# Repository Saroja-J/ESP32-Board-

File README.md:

# 📡 ESP32-WROOM-32D Development Board

A custom **ESP32-WROOM-32D Development Board** designed in **KiCad** for IoT and embedded applications. The board integrates USB-to-UART programming, power management, automatic reset and boot circuitry, and GPIO expansion, providing a compact platform for developing Wi-Fi and Bluetooth-enabled systems.

---

## 📖 Overview

This project is based on the **ESP32-WROOM-32D**, a Wi-Fi and Bluetooth-enabled microcontroller module from Espressif. The board includes a **CH340C USB-to-UART interface**, **LM2596 buck converter**, automatic reset and boot circuitry, GPIO headers, and supporting passive components. It supports **UART, SPI, I²C, PWM, ADC, and GPIO** interfaces, making it suitable for IoT, embedded systems, automation, and rapid prototyping.

---

## 📷 PCB Layout Images

> Add your PCB images below.

| 2-Layer PCB | 4-Layer PCB |
|--------------|--------------|
|  | |

---

## ⚙️ Working

1. The board is powered through USB or an external power source.
2. The **LM2596 buck converter** provides a regulated power supply for the board.
3. The **CH340C** enables USB-to-UART communication for programming and serial debugging.
4. The automatic **Reset** and **Boot** circuit allows easy firmware uploading.
5. After programming, the ESP32 communicates with external peripherals through its GPIO and communication interfaces.

---

## ✨ Features

-  ESP32-WROOM-32D Wi-Fi & Bluetooth Module
-  CH340C USB-to-UART Interface
-  LM2596 Buck Converter
-  Automatic Reset & Boot Circuit
-  GPIO Expansion Headers
-  Supports UART, SPI, I²C, PWM & ADC
-  Designed using KiCad

---

## 🛠️ Components

| Component | Description |
|-----------|-------------|
| ESP32-WROOM-32D | Main Wi-Fi & Bluetooth microcontroller |
| CH340C | USB-to-UART programming interface |
| LM2596 | Buck converter for power regulation |
| USB Connector | Power input and programming |
| NPN Transistors | Automatic Reset & Boot switching |
| Push Buttons | Manual Reset & Boot |
| Capacitors | Power filtering and decoupling |
| Resistors | Pull-up, pull-down and current limiting |
| GPIO Headers | External peripheral connections |

---

## 🚀 Applications

- 🌐 Internet of Things (IoT)
- 🏠 Home Automation
- 🤖 Robotics
- 📡 Wireless Sensor Nodes
- 📊 Data Logging
- 🎛️ Embedded System Development

---

## 📐 Design Details

- Designed by referring to the **ESP32-WROOM-32D Datasheet**, **Hardware Design Guidelines**, and supporting component datasheets.
- Recommended resistor and capacitor values were used throughout the design.
- Decoupling capacitors were placed close to the ESP32 power pins for stable operation.
- A copper-free keep-out zone was maintained around the ESP32 antenna for better RF performance.
- NPN transistors were used for the automatic **Reset** and **Boot** switching circuit.
- The **4-layer PCB** uses copper-filled planes for improved power distribution and grounding.
- Both the **2-layer** and **4-layer** PCB designs were completed with **0 DRC errors**.
- The **LM2596** buck converter was designed using its datasheet. For different input voltages or output currents, refer to the datasheet to select the appropriate inductor and capacitor values.
- An **ESD protection diode** recommended in the ESP32 Hardware Design Guidelines is **not included** in this revision and can be added in future designs.

---

## ⚠️ Warning

This design does **not** include an **ESD protection diode** on the **3.3V supply** near the **ESP32-WROOM-32D**, although it is recommended in the **ESP32 Hardware Design Guidelines**. It can be added in future revisions to improve protection against electrostatic discharge (ESD).

---

## 📄 License

This project is shared for **educational and learning purposes**.

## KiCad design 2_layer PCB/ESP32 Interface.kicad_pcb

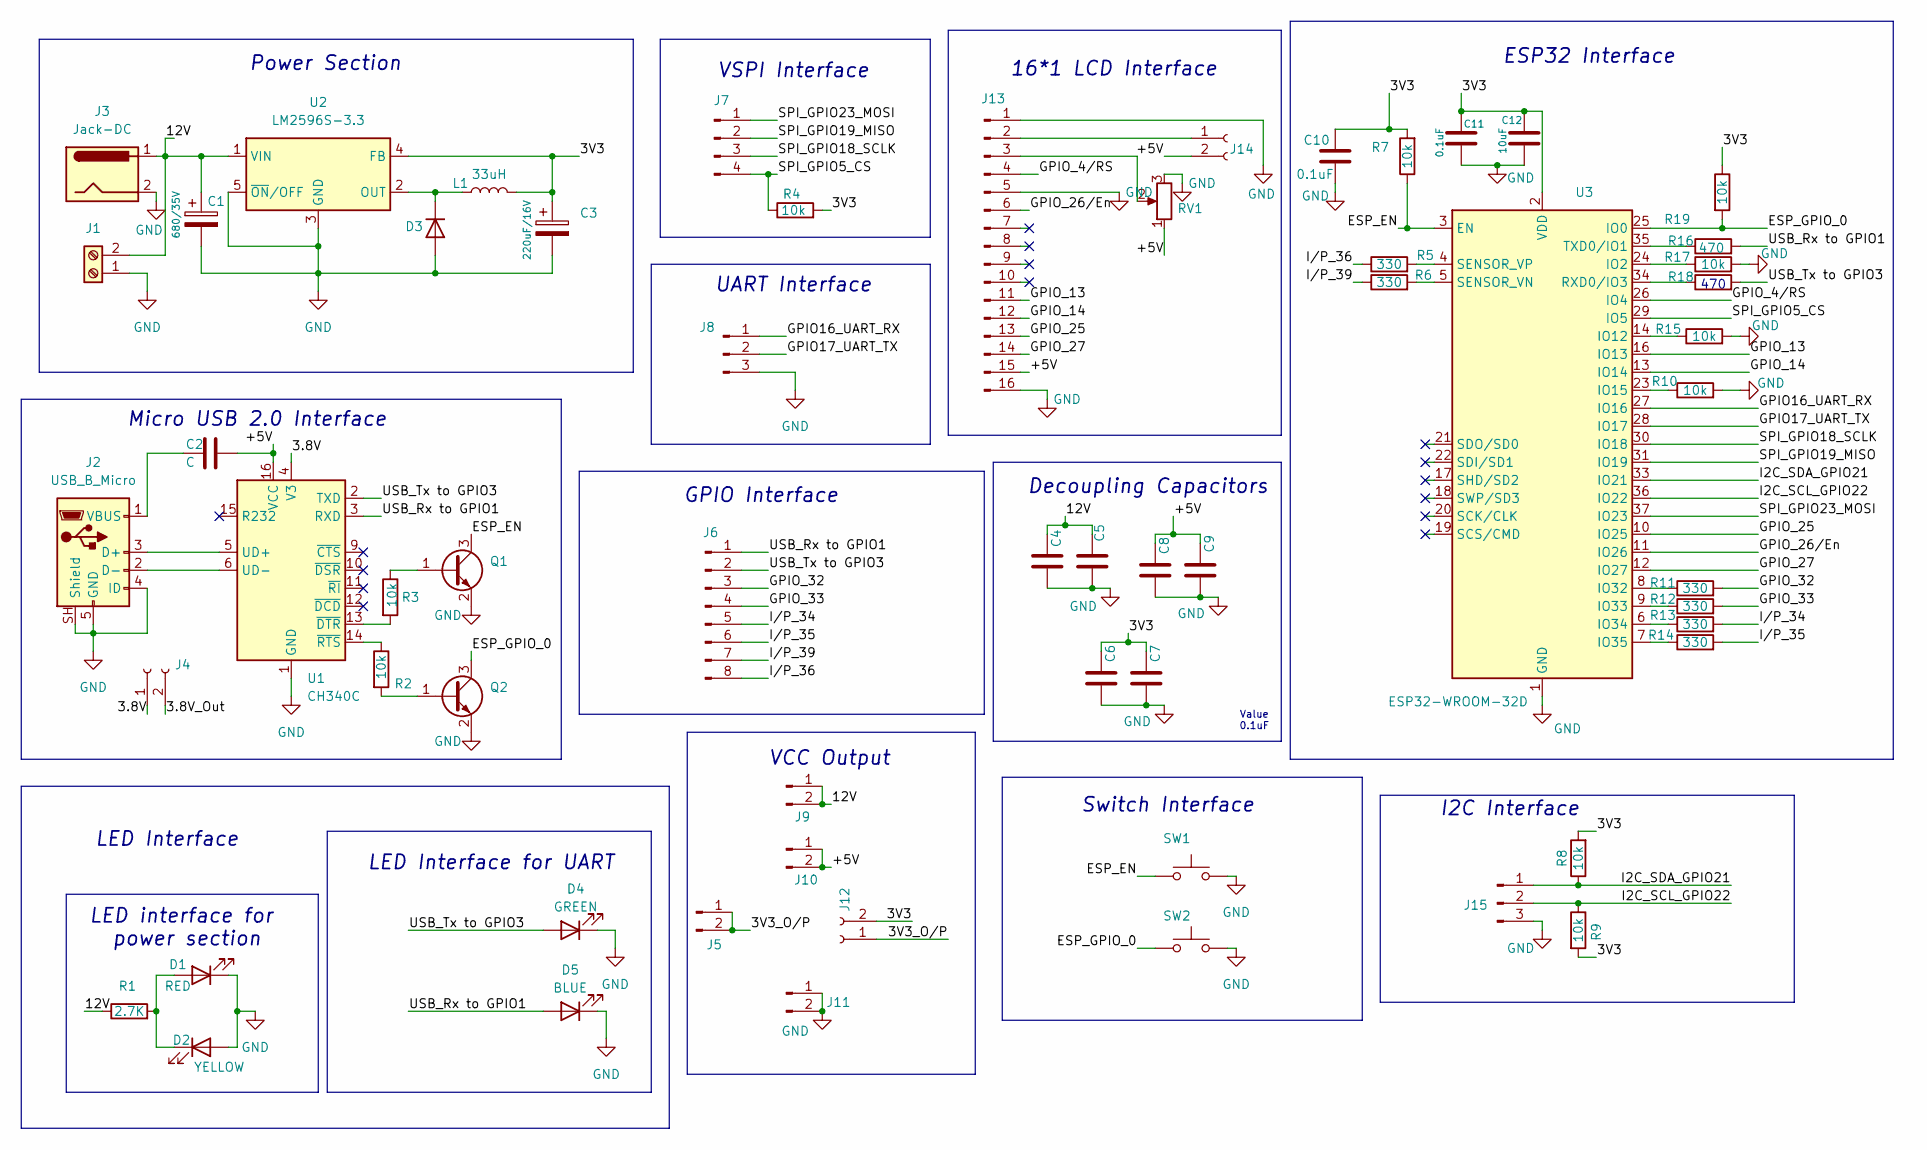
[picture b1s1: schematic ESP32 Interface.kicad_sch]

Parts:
C1: 680/35V; CP_Radial_D8.0mm_P5.00mm
C2, C5, C6, C7, C8, C9: C; C_0805_2012Metric_Pad1.18x1.45mm_HandSolder
C3: 220uF/16V; CP_Radial_D8.0mm_P2.50mm
C4, C10, C11: 0.1uF; C_0805_2012Metric_Pad1.18x1.45mm_HandSolder
C12: 10uF; C_0805_2012Metric_Pad1.18x1.45mm_HandSolder
D1: RED; LED_0805_2012Metric_Pad1.15x1.40mm_HandSolder
D2: YELLOW; LED_0805_2012Metric_Pad1.15x1.40mm_HandSolder
D3: SM518; D_T-1_P2.54mm_Vertical_AnodeUp
D4: GREEN; LED_0805_2012Metric_Pad1.15x1.40mm_HandSolder
D5: BLUE; LED_0805_2012Metric_Pad1.15x1.40mm_HandSolder
J1: Screw_Terminal_01x02; TerminalBlock_Phoenix_MKDS-1,5-2-5.08_1x02_P5.08mm_Horizont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
J2: USB_B_Micro; USB_Micro-AB_Molex_47590-0001
J3: Jack-DC; BarrelJack_SwitchcraftConxall_RAPC10U_Horizontal
J4: Conn_01x02_Socket; PinSocket_1x02_P2.54mm_Vertical
J5, J9, J10, J11: Conn_01x02_Pin; PinSocket_1x02_P2.54mm_Vertical
J6: Conn_01x08_Pin; PinSocket_1x08_P2.54mm_Vertical
J7: Conn_01x04_Pin; PinHeader_1x04_P2.54mm_Vertical
J8: Conn_01x03_Pin; PinSocket_1x03_P2.54mm_Vertical
J12: Conn_01x02_Socket; PinHeader_1x02_P2.54mm_Vertical
J13: Conn_01x16_Pin; PinHeader_1x16_P2.54mm_Vertical
J14: Conn_01x02_Socket; PinHeader_1x02_P2.00mm_Vertical
J15: Conn_01x03_Pin; PinHeader_1x03_P2.54mm_Vertical
L1: 33uH; L_0805_2012Metric_Pad1.05x1.20mm_HandSolder
Q1, Q2: MMBT2222A; SOT-23
R1: 2.7K; R_0805_2012Metric_Pad1.20x1.40mm_HandSolder
R2, R3, R4, R7, R8, R9, R10, R15, R17, R18, R19: 10k; R_0805_2012Metric_Pad1.20x1.40mm_HandSolder
R5, R6, R11, R12, R13, R14: 330; R_0805_2012Metric_Pad1.20x1.40mm_HandSolder
R16: 470; R_0805_2012Metric_Pad1.20x1.40mm_HandSolder
RV1: R_Potentiometer; Potentiometer_Vishay_148-149_Single_Horizontal
SW1, SW2: SW_Omron_B3FS; SW_TH_Tactile_Omron_B3F-100x
U1: CH340C; SOIC-16_3.9x9.9mm_P1.27mm
U2: LM2596S-3.3; TO-263-5_TabPin3
U3: ESP32-WROOM-32D

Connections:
/3.8V: J4.1, U1.4 (V3)
/3.8V_Out: J4.2
/3V3: C3.1, C6.2, C7.2, C10.1, C11.1, C12.1, J12.2, L1.2, R4.2, R7.2, R8.2, R9.2, R19.1, U2.4 (FB), U3.2 (VDD)
/3V3_O/P: J5.1, J5.2, J12.1
/12V: C1.1, C4.2, C5.2, J1.2, J3.1, J9.1, J9.2, R1.1, U2.1 (VIN)
/+5V: C2.1, C8.2, C9.2, J10.1, J10.2, J13.15, J14.2, RV1.1, U1.16 (VCC)
/ESP_EN: Q1.3 (C), R7.1, SW1.1, U3.3 (EN)
/ESP_GPIO_0: Q2.3 (C), R19.2, SW2.1, U3.25 (IO0)
/GPIO16_UART_RX: J8.1, U3.27 (IO16)
/GPIO17_UART_TX: J8.2, U3.28 (IO17)
/GPIO_4/RS: J13.4, U3.26 (IO4)
/GPIO_13: J13.11, U3.16 (IO13)
/GPIO_14: J13.12, U3.13 (IO14)
/GPIO_25: J13.13, U3.10 (IO25)
/GPIO_26/En: J13.6, U3.11 (IO26)
/GPIO_27: J13.14, U3.12 (IO27)
/GPIO_32: J6.3, R11.2
/GPIO_33: J6.4, R12.2
/I2C_SCL_GPIO22: J15.2, R9.1, U3.36 (IO22)
/I2C_SDA_GPIO21: J15.1, R8.1, U3.33 (IO21)
/I/P_34: J6.5, R13.2
/I/P_35: J6.6, R14.2
/I/P_36: J6.8, R5.1
/I/P_39: J6.7, R6.1
/SPI_GPIO5_CS: J7.4, R4.1, U3.29 (IO5)
/SPI_GPIO18_SCLK: J7.3, U3.30 (IO18)
/SPI_GPIO19_MISO: J7.2, U3.31 (IO19)
/SPI_GPIO23_MOSI: J7.1, U3.37 (IO23)
/USB_Rx to GPIO1: D5.2 (A), J6.1, R16.2, U1.3 (RXD)
/USB_Tx to GPIO3: D4.2 (A), J6.2, R18.2, U1.2 (TXD)
GND: C1.2, C3.2, C4.1, C5.1, C6.1, C7.1, C8.1, C9.1, C10.2, C11.2, C12.2, D1.1 (K), D2.2 (A), D3.2 (A), D4.1 (K), D5.1 (K), J1.1, J2.4 (ID), J2.5 (GND), J2.SH (Shield), J3.2, J8.3, J11.1, J11.2, J13.1, J13.5, J13.16, J15.3, Q1.2 (E), Q2.2 (E), R10.2, R15.2, R17.2, RV1.3, SW1.2, SW2.2, U1.1 (GND), U2.3 (GND), U2.5 (~ON/OFF), U3.1 (GND), U3.15 (GND), U3.38 (GND), U3.39 (GND)
unnamed: D1.2 (A), D2.1 (K), R1.2
unnamed: D3.1 (K), L1.1, U2.2 (OUT)
unnamed: J2.3 (D+), U1.5 (UD+)
unnamed: J2.2 (D-), U1.6 (UD-)
unnamed: C2.2, J2.1 (VBUS)
unnamed: J13.2, J14.1
unnamed: J13.3, RV1.2
unnamed: Q1.1 (B), R3.1
unnamed: Q2.1 (B), R2.2
unnamed: R3.2, U1.13 (~DTR)
unnamed: R2.1, U1.14 (~RTS)
unnamed: R17.1, U3.24 (IO2)
unnamed: R15.1, U3.14 (IO12)
unnamed: R10.1, U3.23 (IO15)
unnamed: R11.1, U3.8 (IO32)
unnamed: R12.1, U3.9 (IO33)
unnamed: R13.1, U3.6 (IO34)
unnamed: R14.1, U3.7 (IO35)
unnamed: R18.1, U3.34 (RXD0/IO3)
unnamed: R6.2, U3.5 (SENSOR_VN)
unnamed: R5.2, U3.4 (SENSOR_VP)
unnamed: R16.1, U3.35 (TXD0/IO1)

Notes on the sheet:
Micro USB 2.0 Interface
16*1 LCD Interface
Switch Interface
UART Interface
I2C Interface
LED interface for power section
LED Interface
ESP32 Interface
Value 0.1uF
Power Section
Decoupling Capacitors
GPIO Interface
VSPI Interface
470
VCC Output
LED Interface for UART

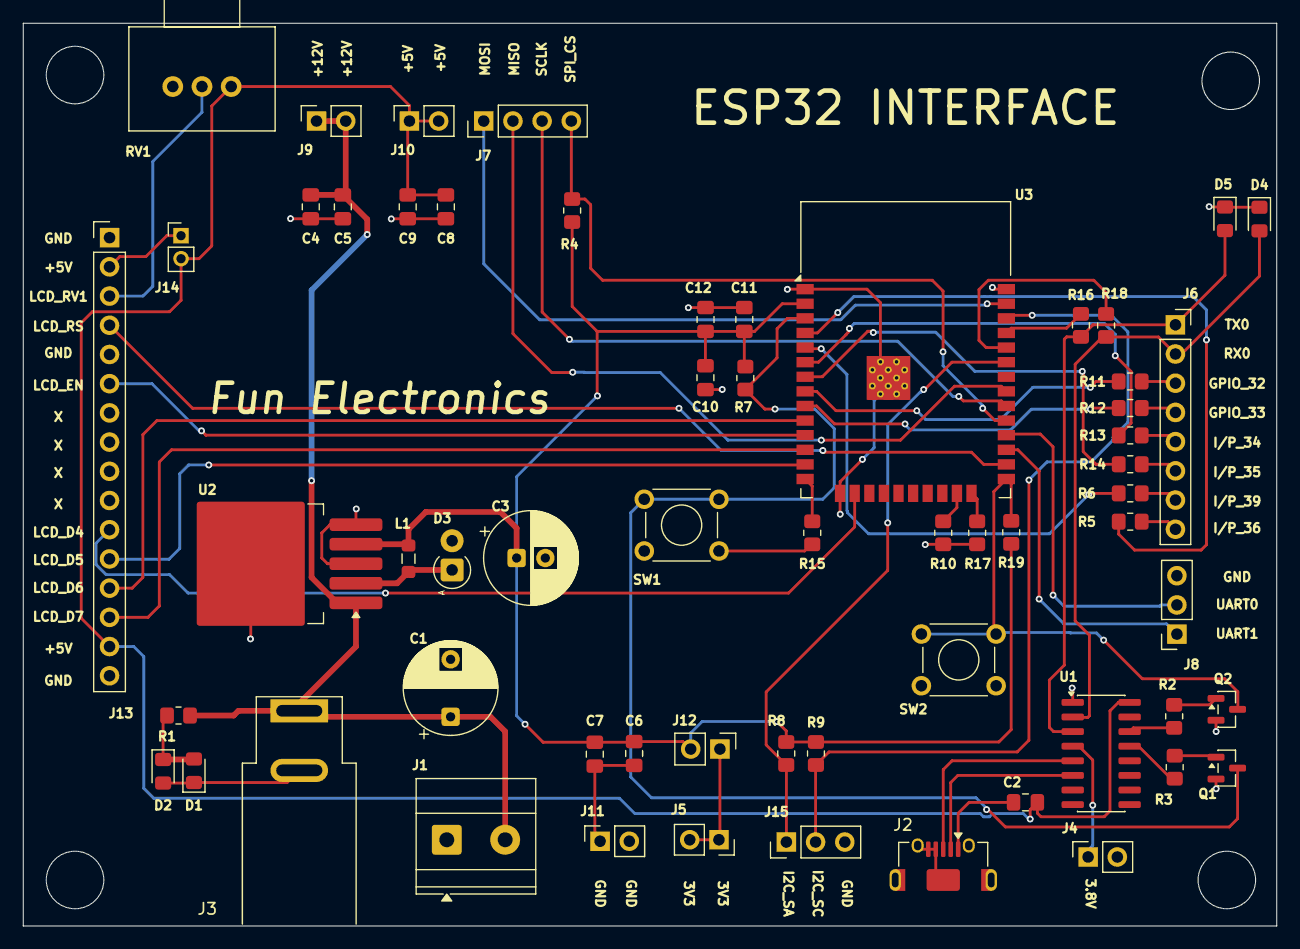
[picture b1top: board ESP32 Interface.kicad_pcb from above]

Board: 2 copper layers, 109.0 x 78.5 mm, 60 parts (0 on the bottom side), 52 nets.
